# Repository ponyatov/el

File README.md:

# `el`
## пособие по аналоговой и цифровой электронике

(c) Dmitry Ponyatov <<dponyatov@gmail.com>> 2023 MIT

github: https://github.com/ponyatov/el

- библиотека компонентов для KiCAD
- примеры проектов
- скрипты

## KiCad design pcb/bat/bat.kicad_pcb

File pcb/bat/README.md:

# `bat`
## MCU-controlled USB/battery pill

check mill tech capabilities with 0.6\0.5mm and lower

USB connectors
- USB/M-1J (DS1104) mini B

smart control
- CH340C (no clock) USB-UART SOP-16
- STM32F030F4P6 TSSOP-20

LiIon charger
- TP4056 = XL4056A Youtai
- AP9101CK6-AYTRG1 SOT26
- FS8205A TSSOP-8 dual n-MOSFET

LED
- LTST-C150KRKT red 1206
- LTST-C150KGKT green 1206

https://github.com/jamesmunns/lipo-stamp
https://www.instructables.com/How-to-Make-Lipo-Battery-Charger-Circuit/

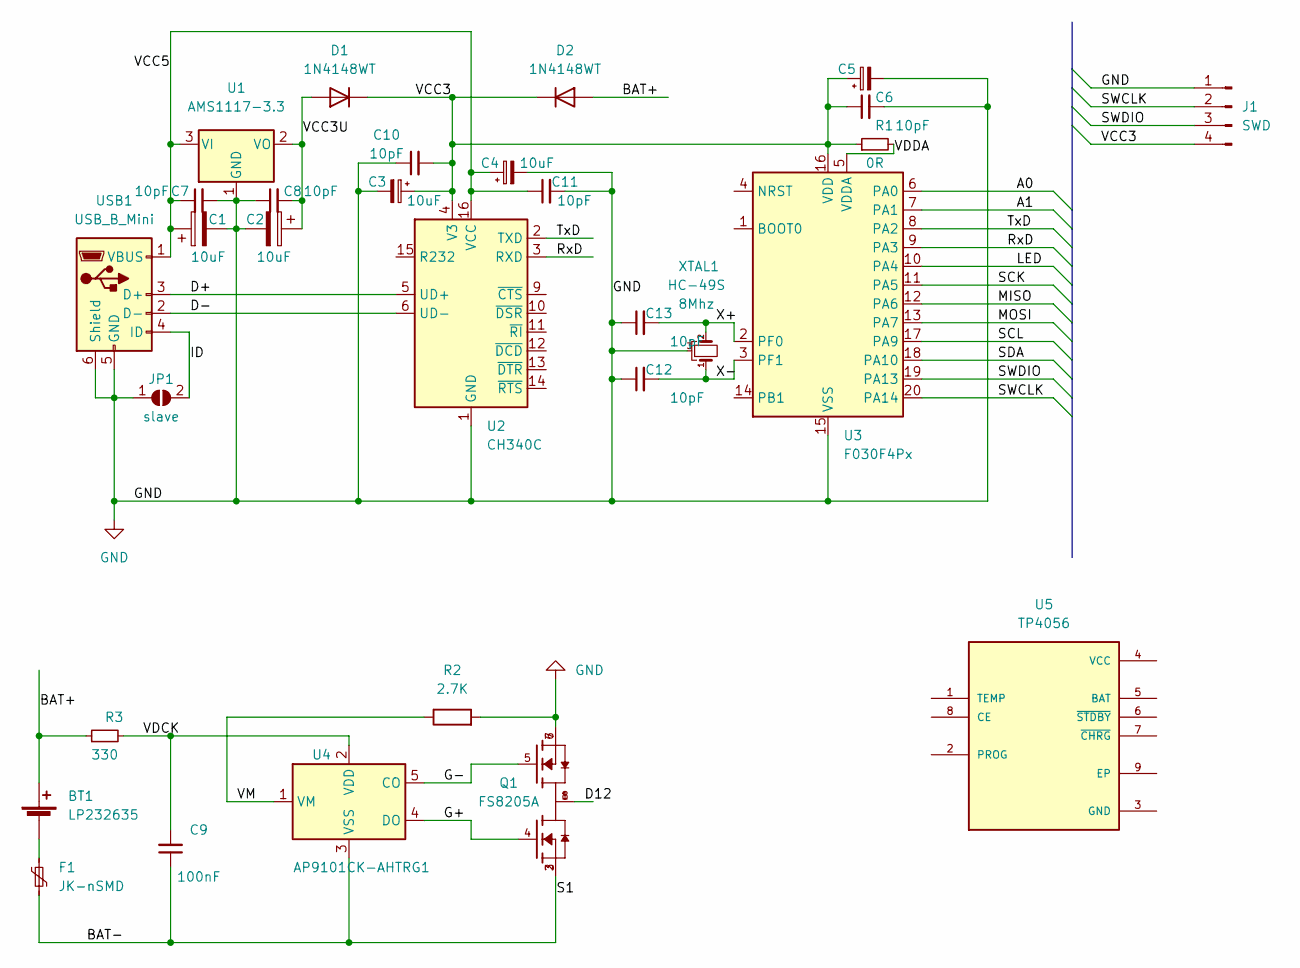
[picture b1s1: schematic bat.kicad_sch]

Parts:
BT1: LP232635; PinHeader_1x02_P2.54mm_Horizontal
C1, C2: 10uF; C_1206_3216Metric_Pad1.33x1.80mm_HandSolder
C3: 10uF; C_0603_1608Metric_Pad1.08x0.95mm_HandSolder
C4: 10uF; C_0805_2012Metric_Pad1.18x1.45mm_HandSolder
C5: C_Polarized_Small; C_0402_1005Metric_Pad0.74x0.62mm_HandSolder
C6, C7, C8, C10, C11, C12, C13: 10pF; R_0402_1005Metric_Pad0.72x0.64mm_HandSolder
C9: 100nF; R_0805_2012Metric_Pad1.20x1.40mm_HandSolder
D1, D2: 1N4148WT; D_SOD-523
F1: JK-nSMD; R_1206_3216Metric
J1: SWD; PinHeader_1x04_P2.54mm_Horizontal
JP1: slave; R_0201_0603Metric
Q1: FS8205A; TSSOP-8_4.4x3mm_P0.65mm; PARTREV 1.9
R1: 0R; R_0201_0603Metric
R2: 2.7K; R_0402_1005Metric_Pad0.72x0.64mm_HandSolder
R3: 330; R_0805_2012Metric_Pad1.20x1.40mm_HandSolder
U1: AMS1117-3.3; SOT-223-3_TabPin2
U2: CH340C; SOIC-16_3.9x9.9mm_P1.27mm
U3: F030F4Px; TSSOP-20_4.4x6.5mm_P0.65mm
U4: AP9101CK-AHTRG1; SOT-23-5
U5: TP4056; SOP127P600X175-9N
USB1: USB_B_Mini; USB_Mini-B_DS1104
XTAL1: 8Mhz; Crystal_HC49-2P_mill; Part HC-49S

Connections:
/A0: U3.6 (PA0)
/A1: U3.7 (PA1)
/BAT+: BT1.2 (+), D2.2 (A), R3.1
/D12: Q1.1, Q1.8
/D+: U2.5 (UD+), USB1.3 (D+)
/D-: U2.6 (UD-), USB1.2 (D-)
/G+: Q1.4, U4.4 (DO)
/G-: Q1.5, U4.5 (CO)
/ID: JP1.2 (B), USB1.4 (ID)
/LED: U3.10 (PA4)
/MISO: U3.12 (PA6)
/MOSI: U3.13 (PA7)
/RST: U3.4 (NRST); also elsewhere on the board
/RxD: U2.3 (RXD), U3.9 (PA3)
/S1: C9.1, F1.2, Q1.2, Q1.3, U4.3 (VSS)
/SCK: U3.11 (PA5)
/SCL: U3.17 (PA9)
/SDA: U3.18 (PA10)
/SWCLK: J1.2, U3.20 (PA14)
/SWDIO: J1.3, U3.19 (PA13)
/TxD: U2.2 (TXD), U3.8 (PA2)
/VCC3: C3.1, C5.1, C6.1, C10.2, D1.1 (K), D2.1 (K), J1.4, R1.1, U2.4 (V3), U3.16 (VDD); also elsewhere on the board
/VCC3U: C2.1, C8.2, D1.2 (A), U1.2 (VO)
/VCC5: C1.1, C4.1, C7.1, C11.1, U1.3 (VI), U2.16 (VCC), USB1.1 (VBUS)
/VDCK: C9.2, R3.2, U4.2 (VDD)
/VDDA: R1.2, U3.5 (VDDA)
/VM: R2.1, U4.1 (VM)
/X+: C13.2, U3.2 (PF0), XTAL1.2
/X-: C12.2, U3.3 (PF1), XTAL1.1
GND: C1.2, C2.2, C3.2, C4.2, C5.2, C6.2, C7.2, C8.1, C10.1, C11.2, C12.1, C13.1, J1.1, JP1.1 (A), Q1.6, Q1.7, R2.2, U1.1 (GND), U2.1 (GND), U3.15 (VSS), USB1.5 (GND), USB1.6 (Shield), XTAL1.3; also elsewhere on the board
unnamed: BT1.1 (-), F1.1

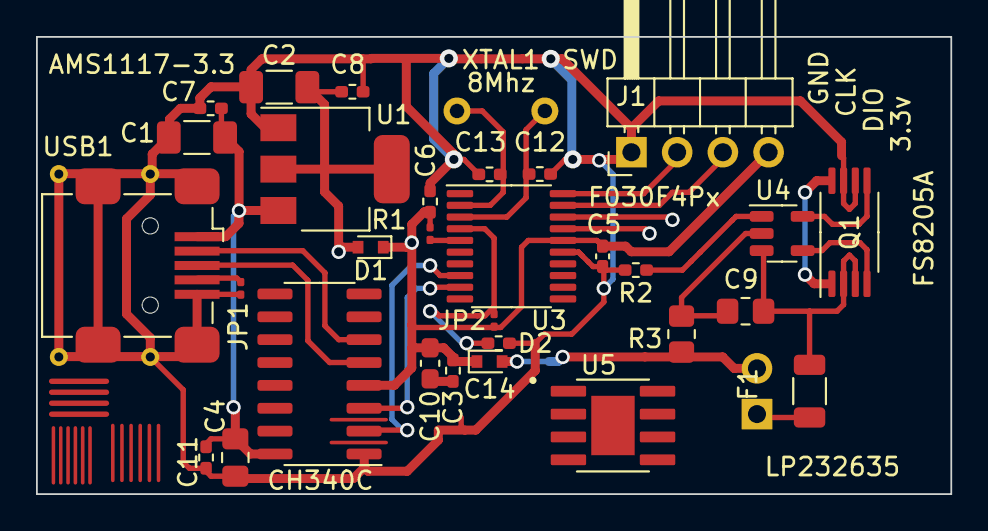
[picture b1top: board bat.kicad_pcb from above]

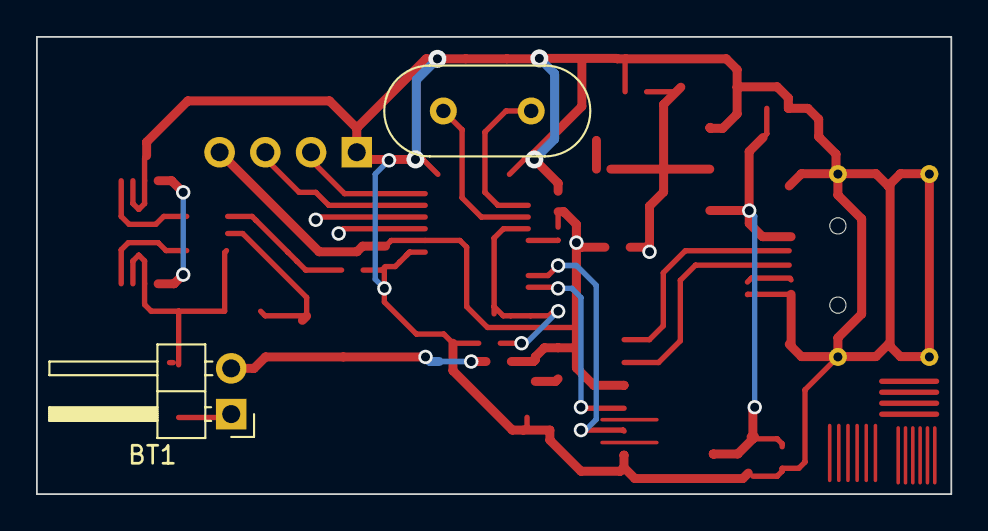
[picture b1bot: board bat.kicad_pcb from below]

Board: 2 copper layers, 50.8 x 25.4 mm, 32 parts (2 on the bottom side), 23 nets.

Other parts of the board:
C14: 10pF; R_0402_1005Metric_Pad0.72x0.64mm_HandSolder
JP2: reset; R_0201_0603Metric

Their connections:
/RST: C14.2, JP2.1 (A); also elsewhere on the board
/VCC3: JP2.2 (B); also elsewhere on the board
GND: C14.1; also elsewhere on the board

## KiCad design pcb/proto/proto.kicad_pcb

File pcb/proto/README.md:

check mill tech capabilities with 0.6\0.5mm and lower

USB connectors
- USB/M-1J (DS1104) mini B

smart control
- CH340C (no clock) USB-UART SOP-16
- STM32F030F4P6 TSSOP-20

LiIon charger
- TP4056 = XL4056A Youtai
- AP9101CK6-AYTRG1 SOT26
- FS8205A TSSOP-8 dual n-MOSFET

LED
- LTST-C150KRKT red 1206
- LTST-C150KGKT green 1206

https://github.com/jamesmunns/lipo-stamp
https://www.instructables.com/How-to-Make-Lipo-Battery-Charger-Circuit/

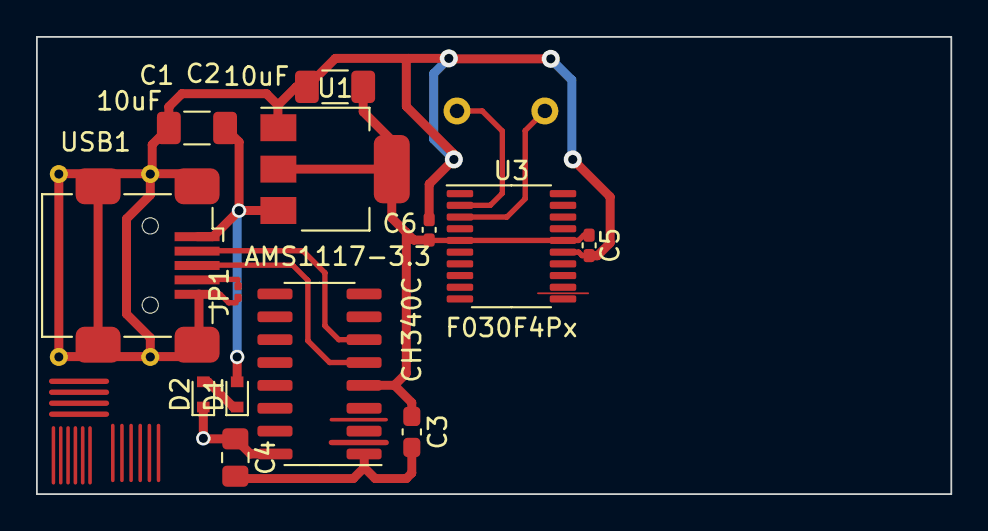
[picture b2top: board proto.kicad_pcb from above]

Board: 2 copper layers, 50.8 x 25.4 mm, 14 parts (1 on the bottom side), 10 nets.

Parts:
C1, C2: 10uF; C_1206_3216Metric_Pad1.33x1.80mm_HandSolder
C3: 0603; C_0603_1608Metric_Pad1.08x0.95mm_HandSolder
C4: 0805; C_0805_2012Metric_Pad1.18x1.45mm_HandSolder
C5, C6: C_Polarized_Small; C_0402_1005Metric_Pad0.74x0.62mm_HandSolder
D1, D2: 1N4148WT; D_SOD-523
JP1: slave; R_0201_0603Metric
U1: AMS1117-3.3; SOT-223-3_TabPin2
U2: CH340C; SOIC-16_3.9x9.9mm_P1.27mm
U3: F030F4Px; TSSOP-20_4.4x6.5mm_P0.65mm
USB1: USB_B_Mini; USB_Mini-B_DS1104
XTAL1: HC-49S; Crystal_HC49-2P_mill

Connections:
/D+: U2.5 (UD+), USB1.3 (D+)
/D-: U2.6 (UD-), USB1.2 (D-)
/GND: C1.2, C2.2, C3.2, C4.2, C5.2, C6.2, JP1.1 (A), U1.1 (GND), U2.1 (GND), U3.15 (VSS), USB1.5 (GND), USB1.6 (Shield)
/ID: JP1.2 (B), USB1.4 (ID)
/VCC3: C2.1, C3.1, C5.1, C6.1, U1.2 (VO), U2.4 (V3), U3.5 (VDDA), U3.16 (VDD)
/VCC5: C4.1, D2.1 (K), U2.16 (VCC)
/VUSB: C1.1, D1.2 (A), U1.3 (VI), USB1.1 (VBUS)
/X+: U3.2 (PF0), XTAL1.2
/X-: U3.3 (PF1), XTAL1.1
unnamed: D1.1 (K), D2.2 (A)

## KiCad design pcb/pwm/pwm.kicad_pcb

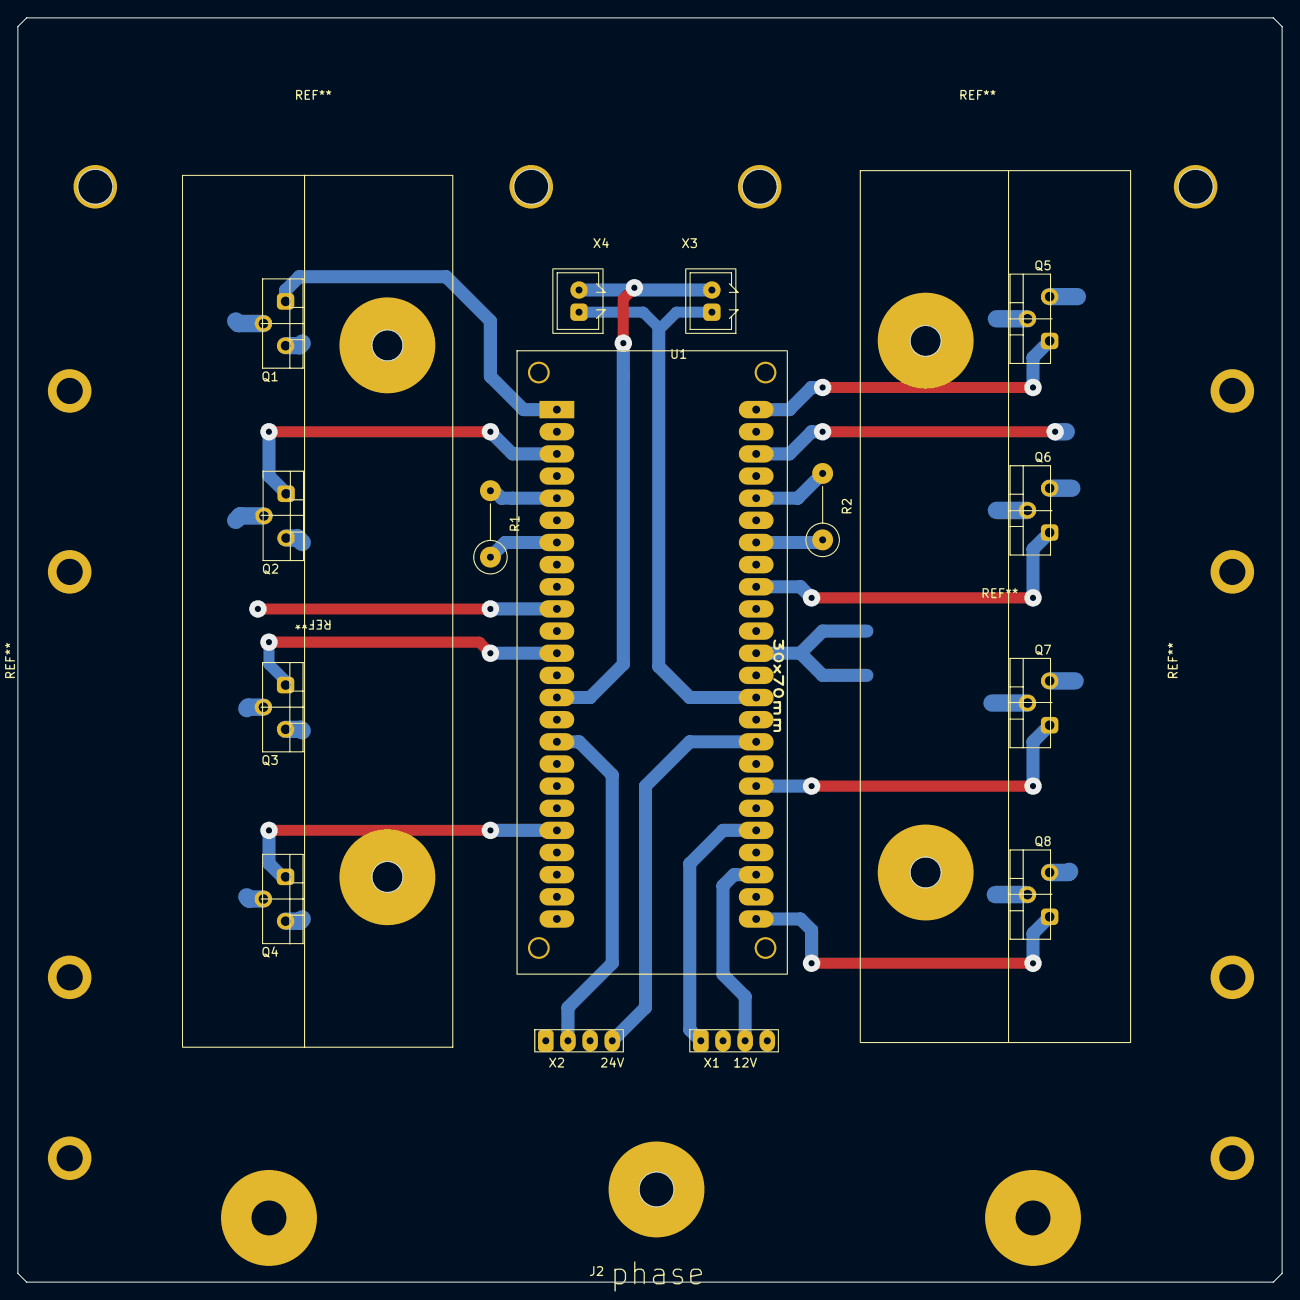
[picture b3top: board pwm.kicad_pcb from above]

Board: 2 copper layers, 145.0 x 145.0 mm, 16 parts (0 on the bottom side), 21 nets.

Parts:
J2: phase; screw_M4
Q1, Q2, Q3, Q4: IRFB4321PBF; TO-220AB
Q5, Q6, Q7, Q8: IRFB4321PBF; TO-220AB_m
R1, R2: B57045K
U1: pwm_meson0
X1: 12V; PLS-4
X2: 24V; PLS-4
X3, X4: Conn_01x02_Male; CWF-2

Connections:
/+12V: U1.22J (+12V), X1.3
/+24V: U1.16J (+24V), X2.4
/+60V: Q1.2 (D), Q2.2 (D), Q3.2 (D), Q4.2 (D), U1.10A (+60V)
/-12V: U1.20J (-12V), X1.1
/-24V: U1.16A (-24V), X2.2
/-60V: Q5.3 (S), Q6.3 (S), Q7.3 (S), Q8.3 (S), U1.3J (-60V)
/G1: Q1.1 (G), U1.1A (Q1)
/G2: Q2.1 (G), U1.3A (Q2)
/G3: Q3.1 (G), U1.12A (Q3)
/G4: Q4.1 (G), U1.20A (Q4)
/G5: Q5.1 (G), U1.1J (Q5)
/G6: Q6.1 (G), U1.9J (Q6)
/G7: Q7.1 (G), U1.18J (Q7)
/G8: Q8.1 (G), U1.24J (Q8)
/fan+: U1.14A (fan+), X3.2, X4.2
/fan-: U1.14J (fan-), X3.1, X4.1
/phase: J2.1, Q1.3 (S), Q2.3 (S), Q3.3 (S), Q4.3 (S), Q5.2 (D), Q6.2 (D), Q7.2 (D), Q8.2 (D), U1.12J (phase)
/t1+: R1.1, U1.7A (t1+)
/t1-: R1.2, U1.5A (t1-)
/t2+: R2.1, U1.7J (t2+)
/t2-: R2.2, U1.5J (t2-)

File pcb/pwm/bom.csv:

"Id";"Designator";"Package";"Quantity";"Designation";"Supplier and ref";
1;"Q8,Q6,Q1,Q7,Q5,Q2,Q4,Q3";"TO-220-3_Vertical";8;"IRFB4321PBF";;;
2;"X3,X4";"CWF-2";2;"Conn_01x02_Male";;;
3;"REF**,REF**";"RQD6010MS";2;"RQD6010MS";;;
4;"X2,X1";"PLS-4";2;"Conn_01x04_Male";;;
5;"R1,R2";"R_Axial_DIN0411_L9.9mm_D3.6mm_P7.62mm_Vertical";2;"B57045K";;;
6;"REF**,REF**";"pwm_radiator";2;"pwm_radiator";;;
7;"U1";"pwm_meson0";1;"pwm_meson0";;;

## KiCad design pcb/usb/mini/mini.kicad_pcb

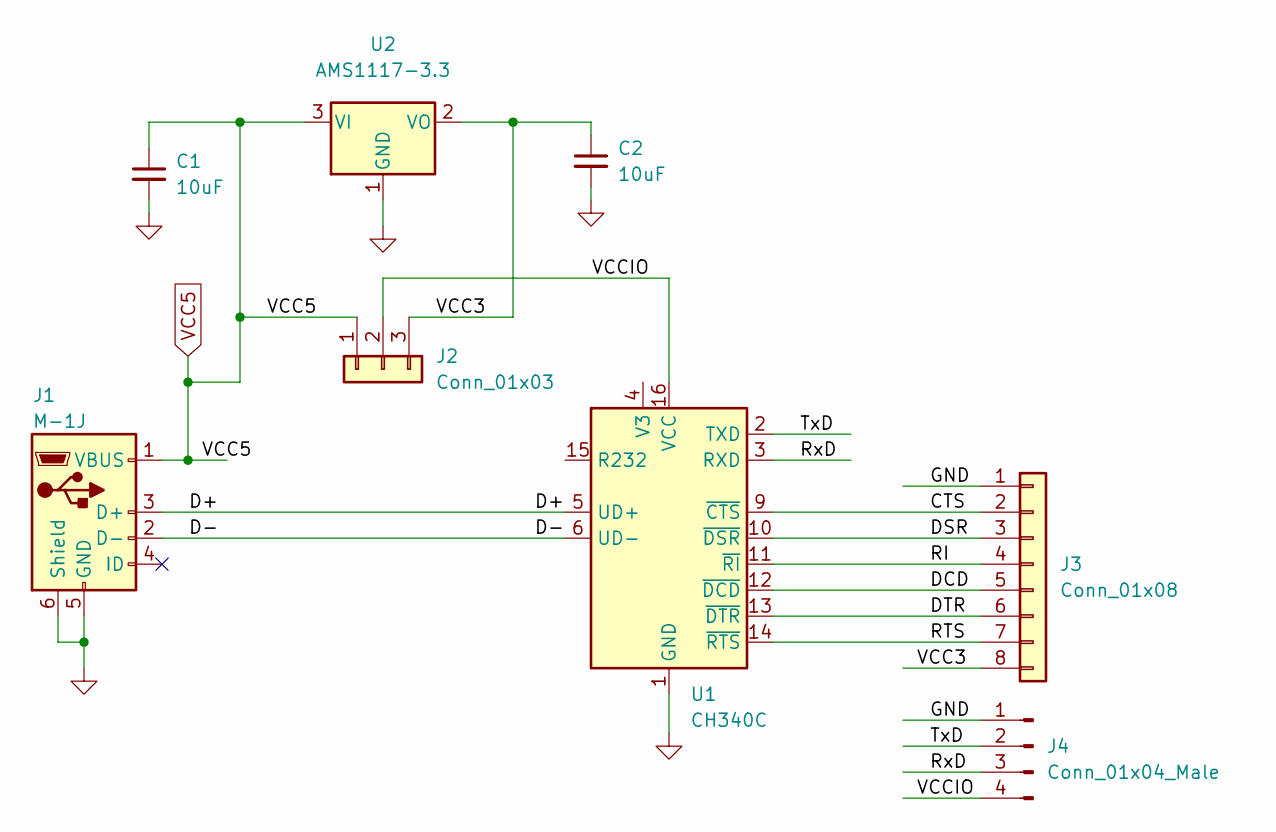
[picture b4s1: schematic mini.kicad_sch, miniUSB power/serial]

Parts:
C1, C2: 10uF; C_0805
J1: M-1J; USB_Mini-B_DS1104
J2: Conn_01x03; PinHeader_1x03_P2.54mm_Vertical
J3: Conn_01x08; PinHeader_1x08_P2.54mm_Horizontal
J4: Conn_01x04_Male; PinHeader_1x04_P2.54mm_Horizontal
U1: CH340C; SOIC-16_3.9x9.9mm_P1.27mm
U2: AMS1117-3.3; SOT-223-3_TabPin2

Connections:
/CTS: J3.2, U1.9 (~CTS)
/D+: J1.3 (D+), U1.5 (UD+)
/D-: J1.2 (D-), U1.6 (UD-)
/DCD: J3.5, U1.12 (~DCD)
/DSR: J3.3, U1.10 (~DSR)
/DTR: J3.6, U1.13 (~DTR)
/RI: J3.4, U1.11 (~RI)
/RTS: J3.7, U1.14 (~RTS)
/RxD: J4.3, U1.3 (RXD)
/TxD: J4.2, U1.2 (TXD)
/VCC3: C2.1, J2.3, J3.8, U2.2 (VO)
/VCCIO: J2.2, J4.4, U1.16 (VCC)
GND: C1.2, C2.2, J1.5 (GND), J1.6 (Shield), J3.1, J4.1, U1.1 (GND), U2.1 (GND)
VCC5: C1.1, J1.1 (VBUS), J2.1, U2.3 (VI)

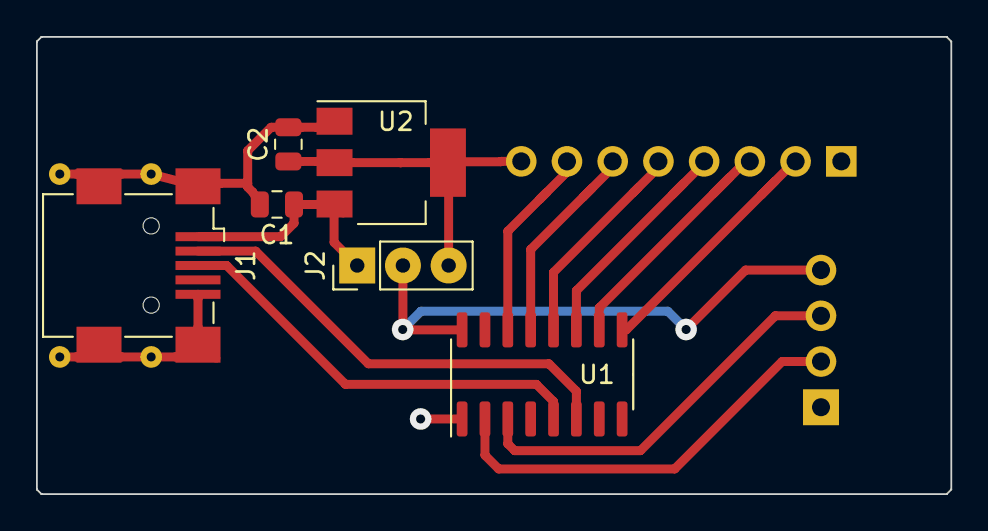
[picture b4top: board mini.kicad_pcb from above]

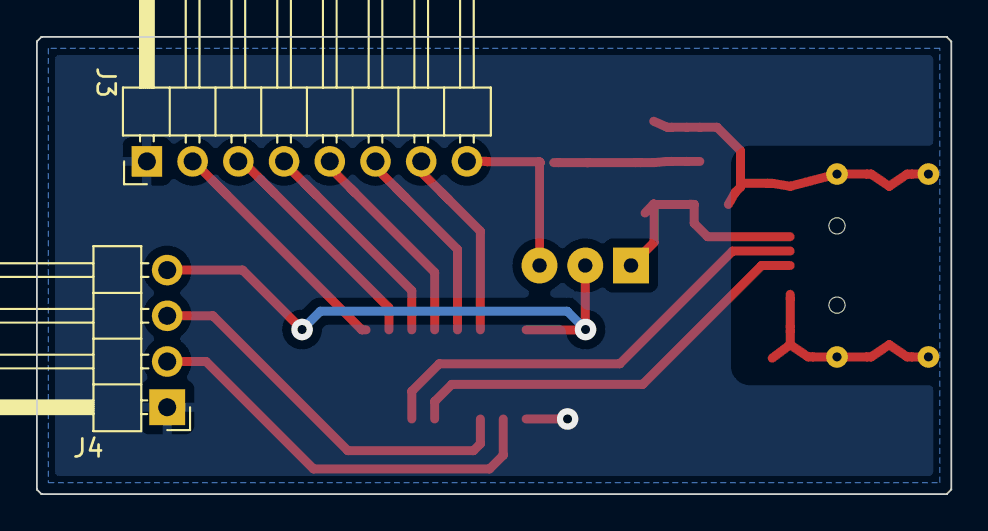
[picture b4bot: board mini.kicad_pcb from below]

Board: 2 copper layers, 50.8 x 25.4 mm, 8 parts (2 on the bottom side), 14 nets.

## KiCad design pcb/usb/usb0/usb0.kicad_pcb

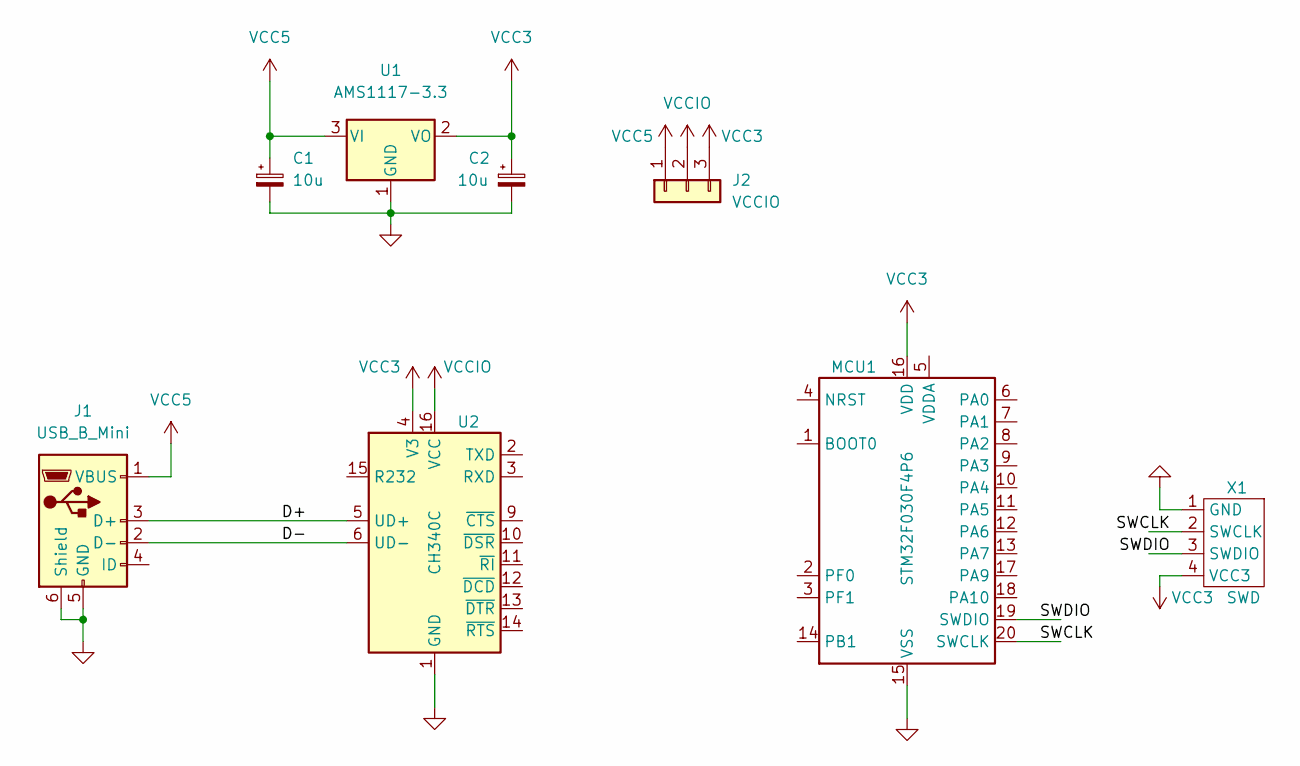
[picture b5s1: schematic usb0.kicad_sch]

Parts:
C1, C2: 10u; C_1206
J1: USB_B_Mini; USB_Mini-B_DS1104
J2: VCCIO; PinHeader_1x03_P2.54mm_Vertical
MCU1: STM32F030F4P6; TSSOP-20_4.4x6.5mm_P0.65mm
U1: AMS1117-3.3; SOT-223-3_TabPin2
U2: CH340C; SOP-16_3.9x9.9mm_P1.27mm
X1: SWD; SWD_R

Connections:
+3.3V: C2.1, J2.3, MCU1.16 (VDD), U1.2 (VO), U2.4 (V3), X1.4 (VCC3)
+5V: C1.1, J1.1 (VBUS), J2.1, U1.3 (VI)
/D+: J1.3 (D+), U2.5 (UD+)
/D-: J1.2 (D-), U2.6 (UD-)
/SWCLK: MCU1.20 (SWCLK), X1.2 (SWCLK)
/SWDIO: MCU1.19 (SWDIO), X1.3 (SWDIO)
GND: C1.2, C2.2, J1.5 (GND), J1.6 (Shield), MCU1.15 (VSS), U1.1 (GND), U2.1 (GND), X1.1 (GND)
VCCIO: J2.2, U2.16 (VCC)

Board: 2 copper layers, 8 parts (1 on the bottom side), 8 nets, no tracks yet.

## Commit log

2013-08-07 + eclipse.project * README
2013-08-07 + CAN/brick breadboard module (ssau/insomnius)
2013-08-13 + USB HEX FT232R USB-<COM breakout board
2013-08-13 + J3 pins
2013-08-13 + USERDVC library dump
2013-08-14 * Proteus lib management
2013-08-14 + USERPKG.lib + sample routing ->LYT
2014-04-13 + tut01 @ http://www.youtube.com/watch?v=dlQL0-8-HFs
2014-04-13 + gitignore
2014-04-18 +lib
2014-04-18 + ARMatura030
2014-04-18 + datasheets
2014-04-18 + FTDI chips
2014-04-18 + lib: Fulling Motor co.
2014-04-18 + STMicroelectronics
2014-04-21 +simple edge finder on opamp R-comparer
2014-04-29 * FTDI FT232RL
2014-04-29 * FT-side fixed
2024-07-09 Merge branch 'shadow' of github.com:ponyatov/el into shadow
    # Conflicts:
    # Makefile
    # lib/config/6.0/fp-lib-table
    # lib/config/6.0/fpedit.json
    # lib/config/6.0/pcbnew.json
    # pcb/pwm/fp-info-cache
